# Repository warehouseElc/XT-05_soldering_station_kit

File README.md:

# XT-05 Soldering station kit
5 in 1 Soldering Rework Station "NOT Unisolder"

This project come for DIYers to make a good and reliable soldering station kit.
it works as independent controller, 
that's mean you can't swap the tip each other like unisolder cause it doesn't have a tip preset.
this come to much complexity for cable management, since i design it to be fully modular.
so... no solder required to disassamble whole unit.
all firmware not originaly made by me, but it's a lot of effort to modded and bugfixes.
if you want to copy or modified any of this resource, 
please let me know the result of your work.
this controller is still upgradable, but i dont have enough time to made this full of feature.

# Main Unit :
  * This unit controlled by atmega328p mount at FrontPanel board, it use I/O to select which controller you wanna uses and activated independent optocoupler for each controller and each signal.
  * ACC remote to turn on acc like fume extractor or etc by push a software latch button.
  * it's also come with one encoder and 2 button to operate the controller.
  * the CTRL switch operated directly to main controller power.
  * when push up & down button at the same time it will lock the I/O.
  * after 2 hour at Lock mode the unit goes to stby mode by switch off the relay main 5v & 12v , as indicator STBY turn green.
  * baypass mode working just for Hotair station.
  * an ESD plug was separated by main groung / AC earth socket.

# This controller contains :

1. Nano solder NT-115.
   this controller use stm32f030f4 work at max 18v supply but the tip it self consume just 15w at 9v.
   i used 12v supply for this and calibrated it for chinese tip. if you want to use jbc original or diffrent vendor you just need re-calibrated it.
     
     Feature : 
     
       * can be use with any c-115 handle or tips.
       * sleep seat.
       * stable & fast respond time.
       * small PCB dimension.
       * less component
       * voltage supply, 3v3 & temp measurment.
       * calibrated menu.
       * error hi/lo-Temp, hi/lo-volt detection.
       
     Known Bug :
       
       * No buzzer/bepper
       * input supply must stable & avoid get voltage spike.
       * using medium-high cost & almost at rare status by now of component.
       * "dont cut" any 3v3 input since it use low-side mosfet it will directly supply 12v to the tip if 3v3 not coming.
       * need some protection if 12v on standby but 3v3 not coming.
       * encoder issue with some incompatible devices.
       * open 3v coming from the seat need more attention. "dont swap with Microsolder seat" 
       
2. Micro solder T-210.
   This controller still use Chinese GVM stc32. in future we can adapt NT-115 controller work for c-210 tip, but !!!
   i need more time to fix a bug and test it.
       
      Feature :
       
        * do i need to explain it ? i dont thing so.

3. iron solder hakko 9series.
    This controller use atmega328p (promini), and run at DC 24v very smoothly.
      
      Feature :
      
        * Tune & Calibrated Menu
        * error screen.
        * easy to use and interactive display.
        * isolated to main power.
        
      Known Bug :
      
        * hard to calibrate cause by slow reading.
        * auto sleep sometimes not working.
        * noisy at heater when start up.
        * no preset temp.
        
4. Hotair 858D.
    This controller use atmega328p (promini), with 700w 220v heater element.
      
      Feature :
      
        * Tune & Calibrated Menu
        * error screen.
        * easy to use and interactive display.
        * add bypass mode to active cool air.
        * isolated to main power
        
      Known Bug :
      
        * hard to calibrate cause by slow reading.
        * seat sleep is lag by 3second.
        * sometimes display get stuck.
        * no preset temp.
        
5. Pre-heater.
   This controller use atmega328p (promini), with 200w/400w 220v heater element.
   (based on Hotair station firmware).
   
      Feature :
      
        * Tune & Calibrated Menu
        * error screen.
        * easy to use and interactive display.
        * isolated to main power

      Known Bug :
      
        * hard to calibrate cause by slow reading.
        * very slow respond.
        * no preset temp.

# Technical Image.

# Test Method :
  * it was 2 years testing by daily workflow until now no magic smoke no fire and no overheat.
  * all controller was test individual function without problem.
  * under heavy load still no problem.
  * unstable main VAC doesn't cause any issue.
  * working almost at 30c room temp no aircond everyday use.
  * standby more than 5 hour everyday.

# Progress on 2023 :
  * get some data by measure at maximum load
  * testing c210 on nano controller.
  * hardware & software bug fixes.
  * make some improvement.
  * added more protection.

# ChangeLog : 

  (2022)
  Firmware 9series v.2.1 Hotair v.1.5 PreHeater v.1.0 (Board v4.0) Nanosolder v.1.2 (Board v.1.1) F.panel v.1.2.1 (Board v.1.4.0) 
  
    * Put all controller in a 1u case.
    * add two extra button as simulated encoder output @10ms using FP_MCU.
    * using 2 PSU, 24v for iron,hotair,Preheater, 12v for nano & micro.
    * output can be use with extention box or just plug to main unit.
    * modified some powerline for controlling using FP_MCU.
        * 2 Relay add to main 220v control directly with power button
        * add relay module for ACC remote.
        * 2 Relay add for 5vreg & 12v main.
   
  (2021)
  Firmware 9series v.2.1 Hotair v.1.5 (Board Version 4.0) 
  
    * change component to SMD as possible
    * SH1106 Oled 1.3" Used For Display
    * Removing class PIDscreen for Hot Air to free some memory
    * Protection on Board
    * thermocouple / Thermoresistor Select on board
    * Fan 24/12volt select on board
    * Custom Front Panel for operated just only 1 encoder, I/O via IDC Socket

# Resource :
  This Project is Upgrade Version from Original.
   * Iron : https://create.arduino.cc/projecthub/sfrwmaker/soldering-iron-controller-for-hakko-907-v-2-fc75d7
   * Nano : https://github.com/Winkelkatze/jbc_nano_solder
   * Hotair & Preheater : https://www.hackster.io/makerbr555/diy-smd-rework-station-28b6f5

# first test of Board v3.0
https://www.youtube.com/watch?v=hSPyxu3pc1E

# first test of Board v4.0
https://youtu.be/PgkWCMdGw-8

# first test of full build (New Firmware)
coming soon...

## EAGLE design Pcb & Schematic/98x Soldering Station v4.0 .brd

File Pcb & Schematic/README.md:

# PCB design status. 
  * PCB v.4.0 ready to use new firmware.
  * PCB v.4.0 can use also for preheater firmware.
  * PCB Front panel & nano not yet updated "need fix & redesign"

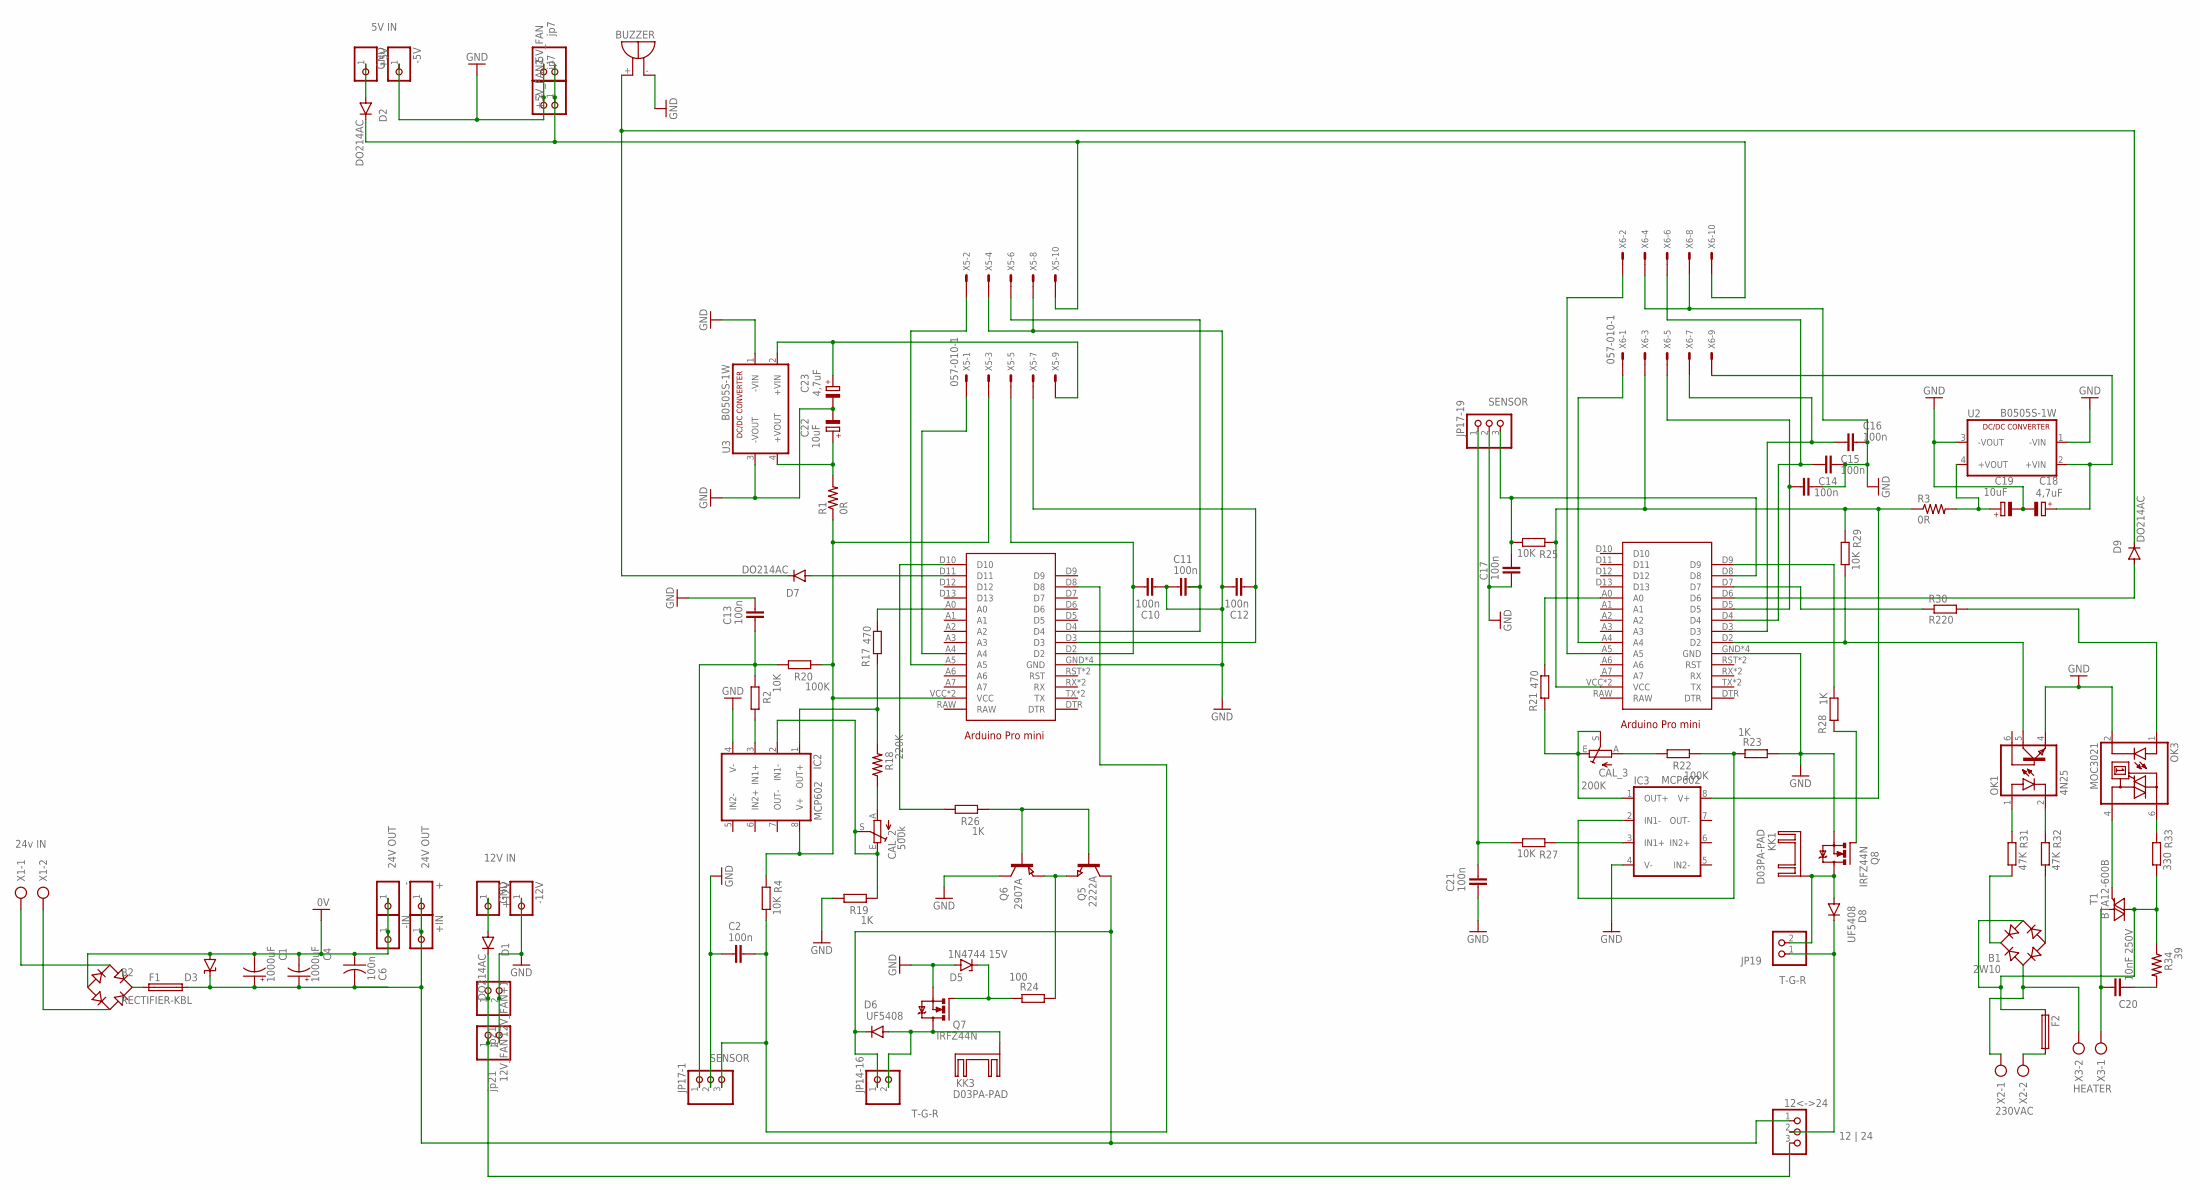
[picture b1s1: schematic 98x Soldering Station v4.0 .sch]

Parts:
5V_FAN: jp7; 1X02
12<->24: 12 | 24; 1X03
12V_FAN, 12V_FAN+1: jp21; 1X02
+: 24V OUT; 1X01
+5V: 5V IN; 1X01
+5V_FAN1: jp7; 1X02
+12V: 12V IN; 1X01
+IN: 24V OUT; 1X01
-, -5V, -12V: GND; 1X01
-IN: GND; 1X01
ARDUINO2: 907 solder; ARDUINO_PRO_MINI
ARDUINO3: HotAir; ARDUINO_PRO_MINI
B1: 2W10; RB1A
B2: RECTIFIER-KBL; KBL
BUZZER: BUZZER; F/TMB
C1, C4: 1000uF; E5-13
C2, C10, C11, C12, C13, C14, C15, C16, C17, C21: 100n; C0805
C6: 100n; C1206K
C18, C23: 4,7uF; B/3528-21R
C19, C22: 10uF; B/3528-21R
C20: 10nF 250V; C10B4
CAL_2: 500k; S64W
CAL_3: 200K; S64W
D1, D2, D7, D9: DO214AC
D3: SUPPRESSOR-SMBJ; SMBJ
D5: 1N4744 15V; DO41Z10
D6, D8: UF5408; SMC
F1, F2: TE5
IC2, IC3: MCP602; DIL08
JP14-16, JP19: T-G-R; 1X02
JP17-1, JP17-19: SENSOR; 1X03
KK1, KK3: D03PA-PAD
OK1: 4N25; DIL06
OK3: MOC3021; DIL06
Q5: 2222A; SOT23
Q6: 2907A; SOT23
Q7, Q8: IRFZ44N; TO220BV
R1, R3: 0R; M0805
R2, R4, R25, R27, R29: 10K; R0805
R17, R21: 470; R0805
R18: 220K; R0805
R19, R23, R26, R28: 1K; R0805
R20, R22: 100K; R0805
R24: 100; R0805
R30: R220; R0805
R31, R32: 47K; M1206
R33: 330; M1206
R34: 39; 0411/15
T1: BTA12-600B; TO220BV
U2, U3: B0505S-1W; 4SIL
X1: 24v IN; AK500/2-H
X2: 230VAC; AK500/2-H
X3: HEATER; AK500/2-H
X5, X6: 057-010-1

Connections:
0V: -.1, -IN.1, B2.-, C1.-, C4.-, C6.1, D3.A
GND: 5V_FAN.2, 12V_FAN.2, 12V_FAN+1.2, +5V_FAN1.2, -5V.1, -12V.1, ARDUINO2.GND, ARDUINO2.GND@1 (GND), ARDUINO2.GND@2 (GND), ARDUINO2.GND@3 (GND), ARDUINO3.GND, ARDUINO3.GND@1 (GND), ARDUINO3.GND@2 (GND), ARDUINO3.GND@3 (GND), BUZZER.-, C2.2, C10.2, C11.2, C12.1, C13.1, C14.2, C15.2, C16.2, C17.2, C18.-, C19.-, C21.2, C22.-, C23.-, D5.A, IC2.4 (V-), IC3.4 (V-), JP17-1.2, JP17-19.2, OK1.4 (EMI), OK3.2 (C), Q6.3 (C), Q7.S, Q8.S, R19.1, R23.1, U2.1 (-VIN), U2.3 (-VOUT), U3.1 (-VIN), U3.3 (-VOUT), X5.4, X5.8, X6.4, X6.8
unnamed: D6.A, JP14-16.2, KK3.B, Q7.D
unnamed: B2.+, F1.1
unnamed: 12<->24.3, 12V_FAN.1, 12V_FAN+1.1, D1.C
unnamed: C22.+, R1.2, U3.4 (+VOUT)
unnamed: C19.+, R3.2, U2.4 (+VOUT)
unnamed: IC2.3 (IN1+), R2.1
unnamed: B2.AC2, X1.2
unnamed: B2.AC1, X1.1
unnamed: F2.2, X2.2
unnamed: +12V.1, D1.A
unnamed: +5V.1, D2.A
unnamed: ARDUINO2.D8, C2.1, JP17-1.3, R4.2
unnamed: 12<->24.1, +.1, +IN.1, C1.+, C4.+, C6.2, D3.C, D6.C, F1.2, JP14-16.1, Q5.3 (C)
unnamed: ARDUINO2.A4, X5.1
unnamed: ARDUINO2.A5, X5.2
unnamed: BUZZER.+, D7.C, D9.C
unnamed: ARDUINO3.D7, R30.2
unnamed: ARDUINO2.D3, C12.2, X5.7
unnamed: C23.+, U3.2 (+VIN), X5.9
unnamed: Q5.2 (E), Q6.2 (E), R24.1
unnamed: C18.+, U2.2 (+VIN), X6.9
unnamed: 12<->24.2, D8.C, JP19.1
unnamed: 5V_FAN.1, +5V_FAN1.1, D2.C, X5.10, X6.10
unnamed: IC2.1 (OUT+), R17.1, R18.2
unnamed: ARDUINO2.D2, C10.1, X5.5
unnamed: ARDUINO2.D4, C11.1, X5.6
unnamed: ARDUINO2.D11, D7.A
unnamed: ARDUINO2.A0, R17.2
unnamed: ARDUINO3.A0, R21.2
unnamed: CAL_2.A, R18.1
unnamed: CAL_2.E, CAL_2.S, IC2.2 (IN1-), R19.2
unnamed: CAL_3.E, CAL_3.S, IC3.1 (OUT+), R21.1
unnamed: C13.2, JP17-1.1, R2.2, R20.1
unnamed: ARDUINO2.D10, R26.1
unnamed: Q5.1 (B), Q6.1 (B), R26.2
unnamed: D5.C, Q7.G, R24.2
unnamed: CAL_3.A, R22.1
unnamed: ARDUINO3.D8, C17.1, JP17-19.3, R25.2
unnamed: ARDUINO3.D5, C14.1, X6.5
unnamed: ARDUINO3.D4, C15.1, X6.6
unnamed: ARDUINO3.D3, C16.1, X6.7
unnamed: ARDUINO3.A4, X6.1
unnamed: ARDUINO3.A5, X6.2
unnamed: ARDUINO3.D9, R28.2
unnamed: IC3.2 (IN1-), R22.2, R23.2
unnamed: IC3.3 (IN1+), R27.1
unnamed: C21.1, JP17-19.1, R27.2
unnamed: D8.A, JP19.2, KK1.B, Q8.D
unnamed: OK3.4 (A1), T1.G
unnamed: Q8.G, R28.1
unnamed: ARDUINO3.D2, OK1.5 (COL), R29.2
unnamed: ARDUINO3.D6, D9.A
unnamed: ARDUINO3.VCC, ARDUINO3.VCC@1 (VCC), IC3.8 (V+), R3.1, R25.1, R29.1, X6.3
unnamed: OK3.1 (A), R30.1
unnamed: OK3.6 (A2), R33.1
unnamed: B1.AC2, F2.1, R33.2, R34.1, T1.T2 (A2)
unnamed: OK1.2 (C), R32.1
unnamed: OK1.1 (A), R31.1
unnamed: B1.+, R31.2
unnamed: B1.-, R32.2
unnamed: C20.1, T1.T1 (A1), X3.1
unnamed: C20.2, R34.2
unnamed: B1.AC1, X2.1, X3.2
unnamed: ARDUINO2.VCC, ARDUINO2.VCC@1 (VCC), IC2.8 (V+), R1.1, R4.1, R20.2, X5.3

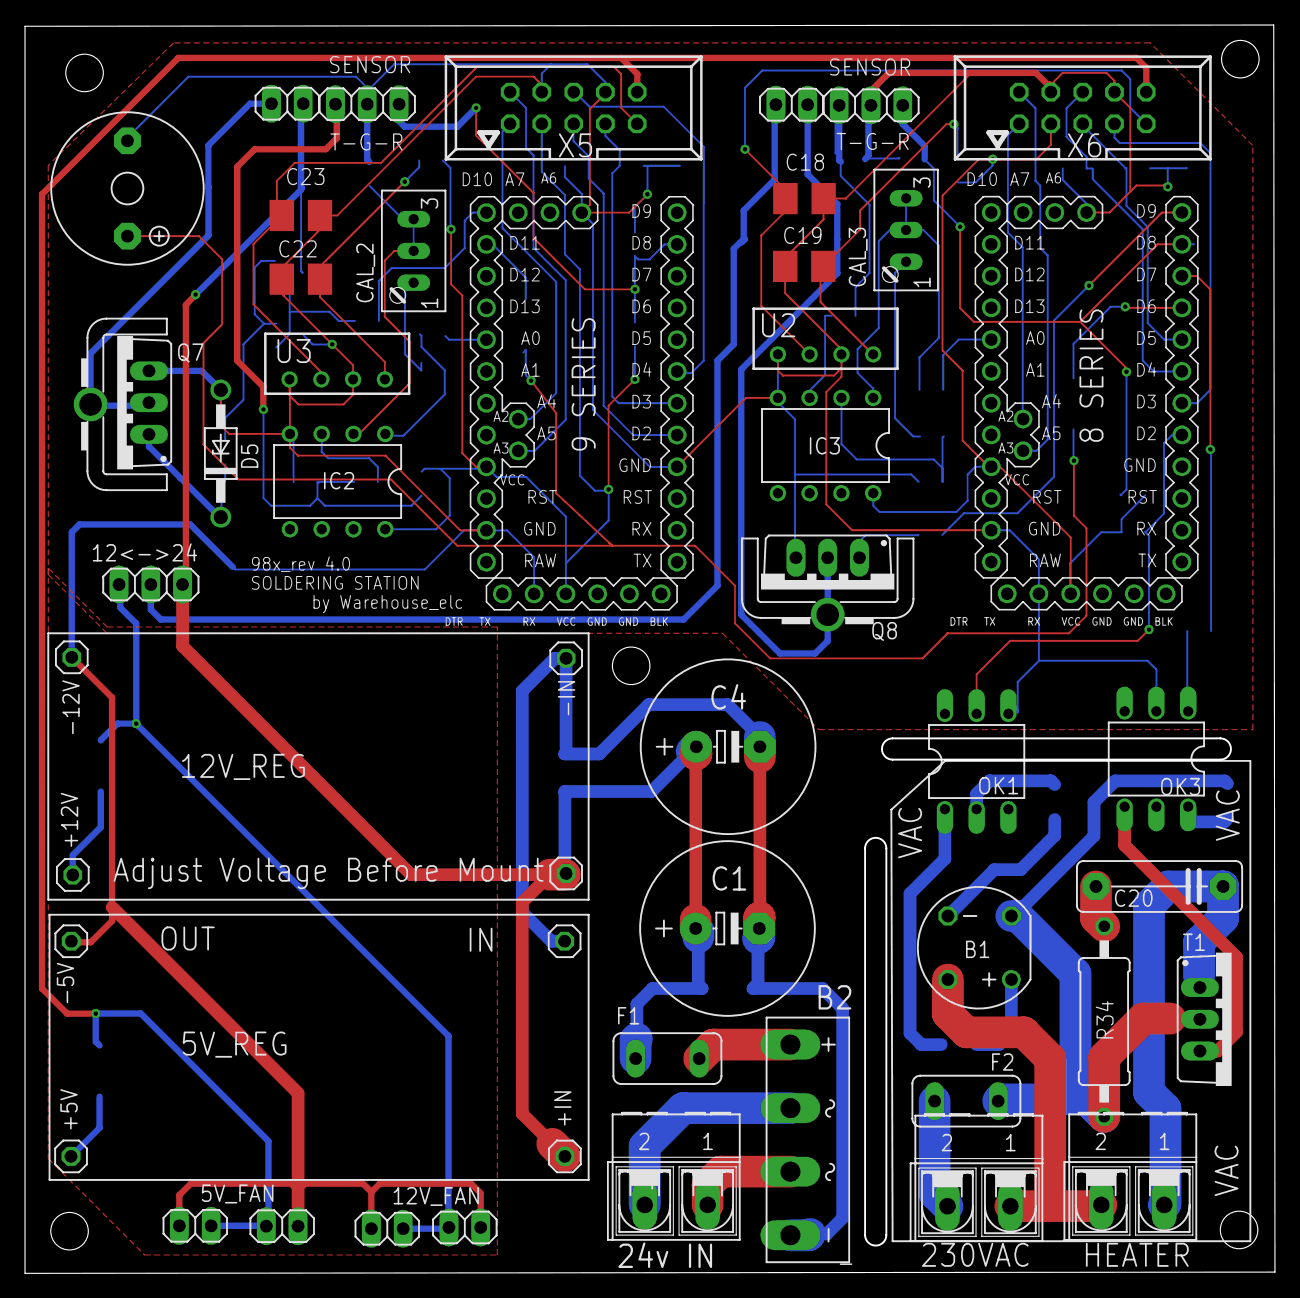
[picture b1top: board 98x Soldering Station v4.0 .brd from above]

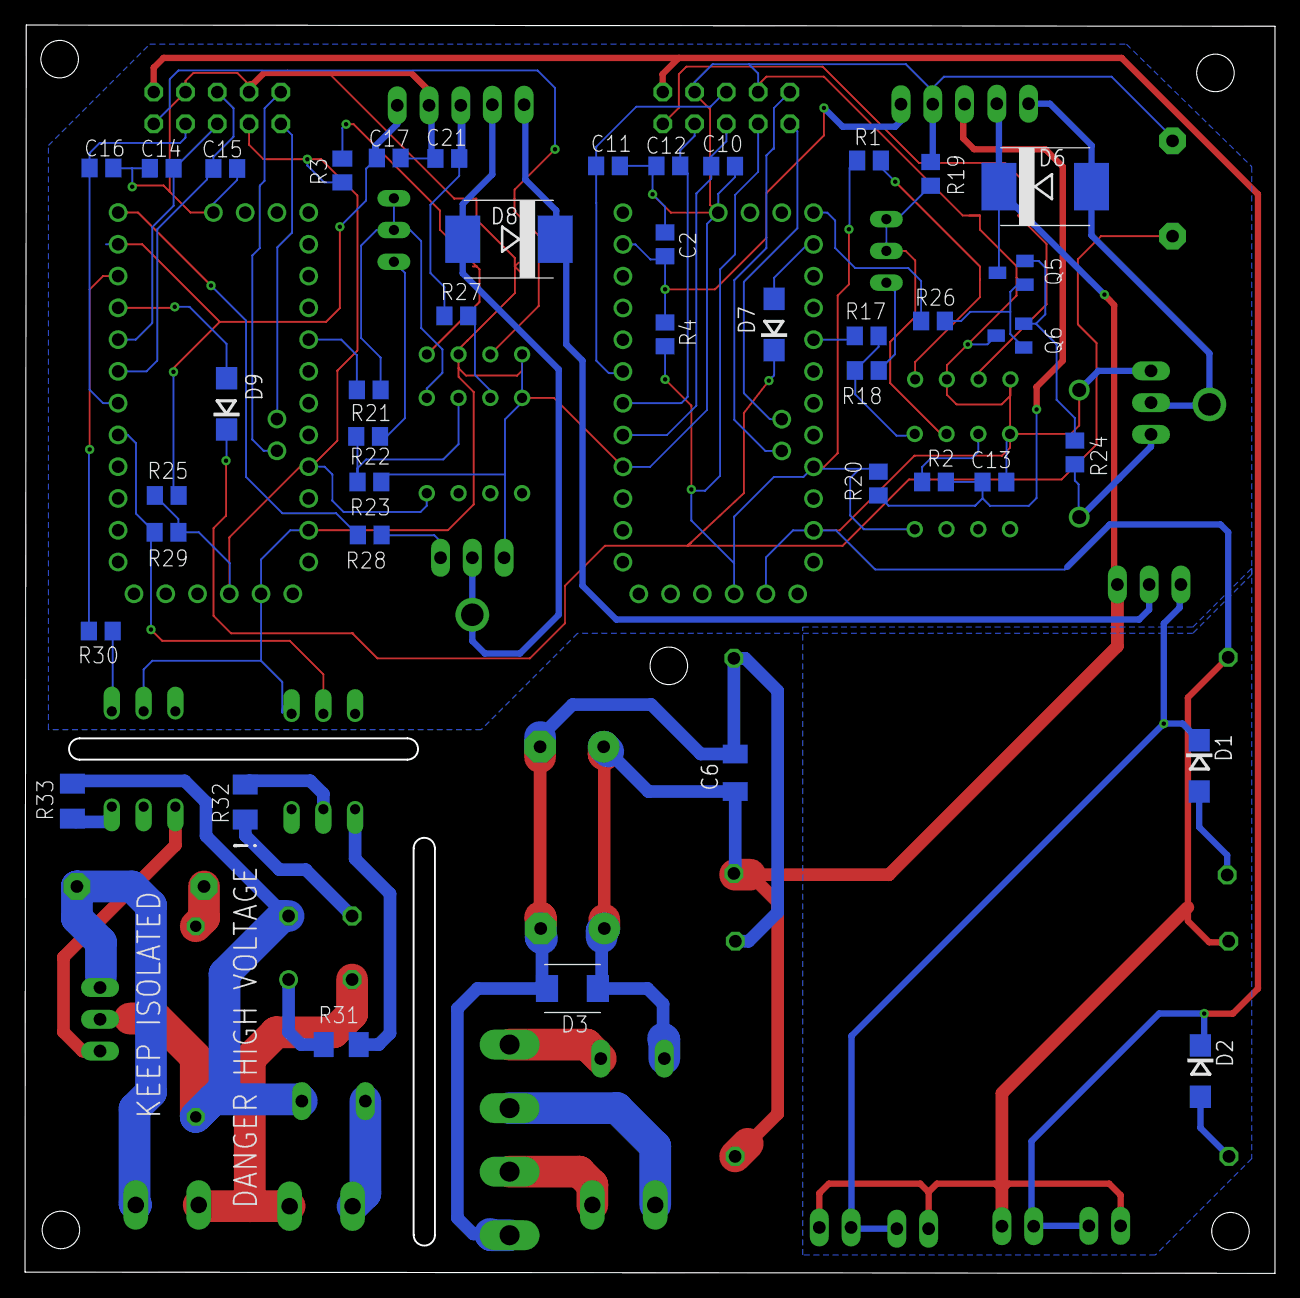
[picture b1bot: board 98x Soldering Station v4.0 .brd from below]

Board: 2 copper layers, 99.8 x 99.6 mm, 92 parts (41 on the bottom side), 66 nets.

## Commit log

2022-11-12 FrontPanel.ino
2022-11-12 Rename 6_Buttonselector_Oled.ino to Front_Panel.ino
    firmware for front panel control
2022-12-08 Update Front_Panel.ino
    add vac sens
2022-12-08 Update Front_Panel.ino
    https://wokwi.com/projects/350487167572640339
2022-12-13 Create XT-05 soldering station kit
2022-12-16 Rename Status.md to README.md
2022-12-16 Rename Preheater_rev4.1v.1.0.ino to Preheater_rev4.0_v.1.0.ino
